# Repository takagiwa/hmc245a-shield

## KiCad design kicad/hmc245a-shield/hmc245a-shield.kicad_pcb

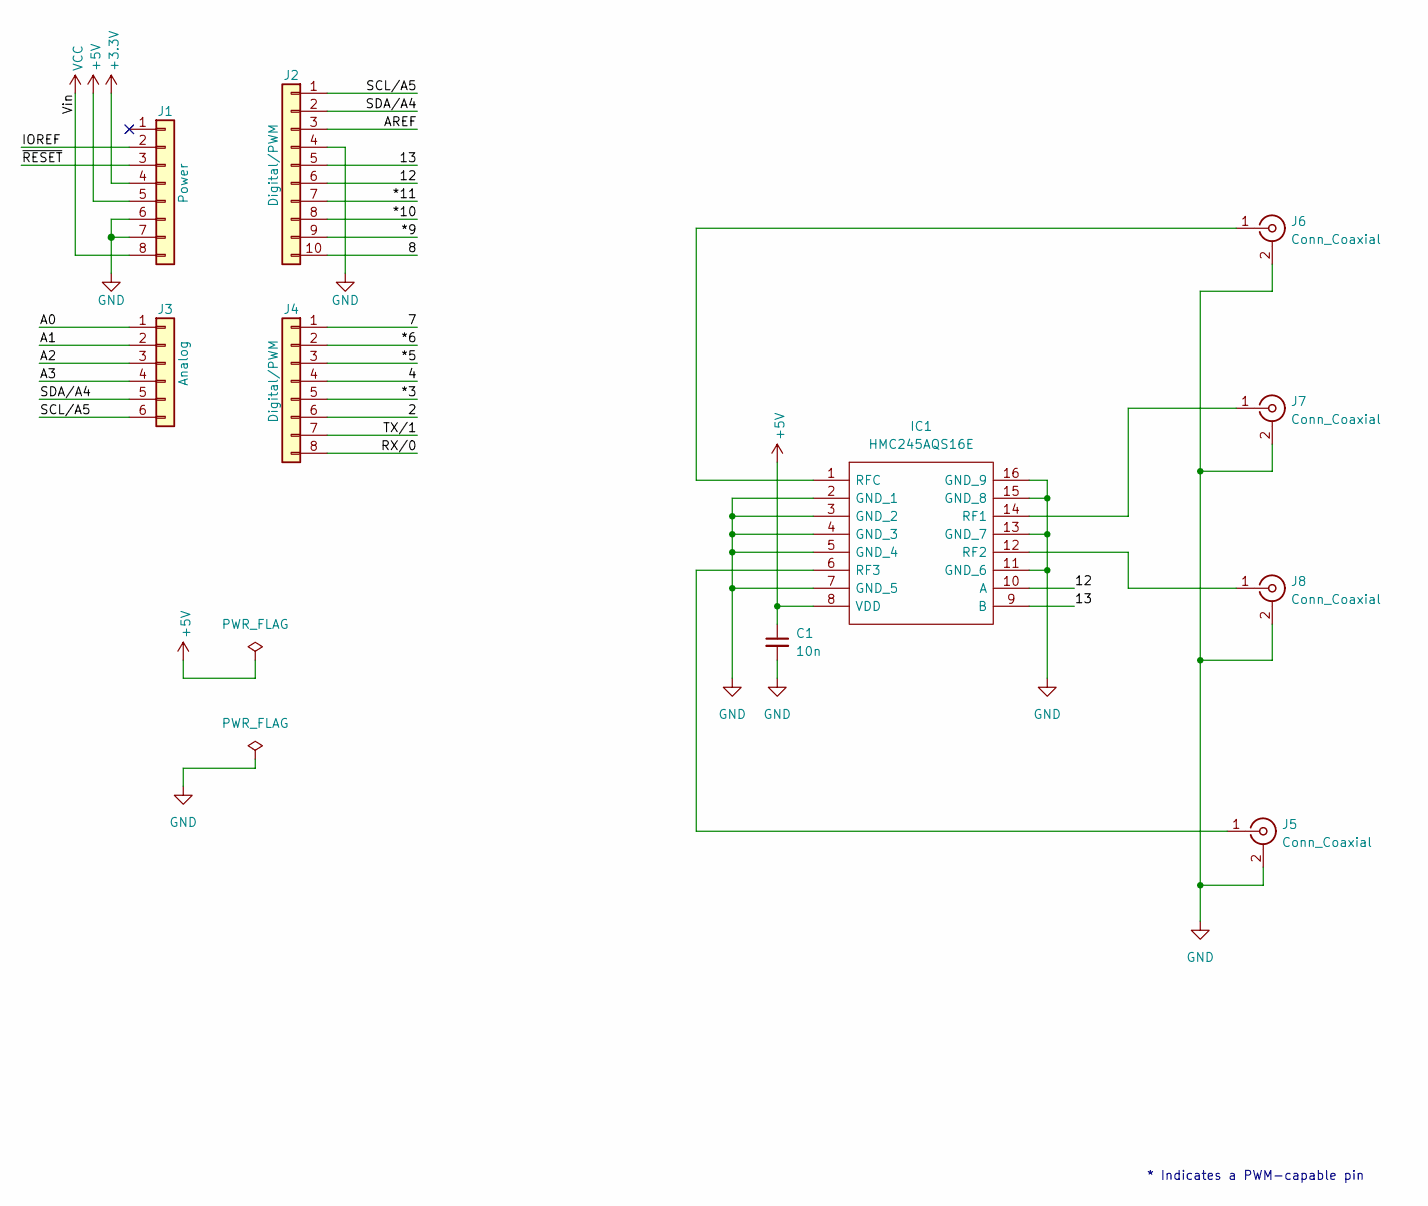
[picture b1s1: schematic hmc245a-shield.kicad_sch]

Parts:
C1: 10n; C_0805_2012Metric_Pad1.18x1.45mm_HandSolder
IC1: HMC245AQS16E; SOP64P600X175-16N; Mouser Part Number 584-HMC245AQS16E
J1: Power; PinSocket_1x08_P2.54mm_Vertical
J2: Digital/PWM; PinSocket_1x10_P2.54mm_Vertical
J3: Analog; PinSocket_1x06_P2.54mm_Vertical
J4: Digital/PWM; PinSocket_1x08_P2.54mm_Vertical
J5, J6, J7, J8: Conn_Coaxial; SMA_Amphenol_901-144_Vertical

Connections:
+3V3: J1.4
+5V: C1.1, IC1.8 (VDD), J1.5
/2: J4.6
/4: J4.4
/7: J4.1
/8: J2.10
/12: IC1.10 (A), J2.6
/13: IC1.9 (B), J2.5
/*3: J4.5
/*5: J4.3
/*6: J4.2
/*9: J2.9
/*10: J2.8
/*11: J2.7
/A0: J3.1
/A1: J3.2
/A2: J3.3
/A3: J3.4
/AREF: J2.3
/IOREF: J1.2
/RX/0: J4.8
/SCL/A5: J2.1, J3.6
/SDA/A4: J2.2, J3.5
/TX/1: J4.7
/~RESET: J1.3
GND: C1.2, IC1.2 (GND_1), IC1.3 (GND_2), IC1.4 (GND_3), IC1.5 (GND_4), IC1.7 (GND_5), IC1.11 (GND_6), IC1.13 (GND_7), IC1.15 (GND_8), IC1.16 (GND_9), J1.6, J1.7, J2.4, J5.2 (Ext), J6.2 (Ext), J7.2 (Ext), J8.2 (Ext)
unnamed: IC1.1 (RFC), J6.1 (In)
unnamed: IC1.6 (RF3), J5.1 (In)
unnamed: IC1.12 (RF2), J8.1 (In)
unnamed: IC1.14 (RF1), J7.1 (In)
VCC: J1.8

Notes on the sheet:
* Indicates a PWM-capable pin

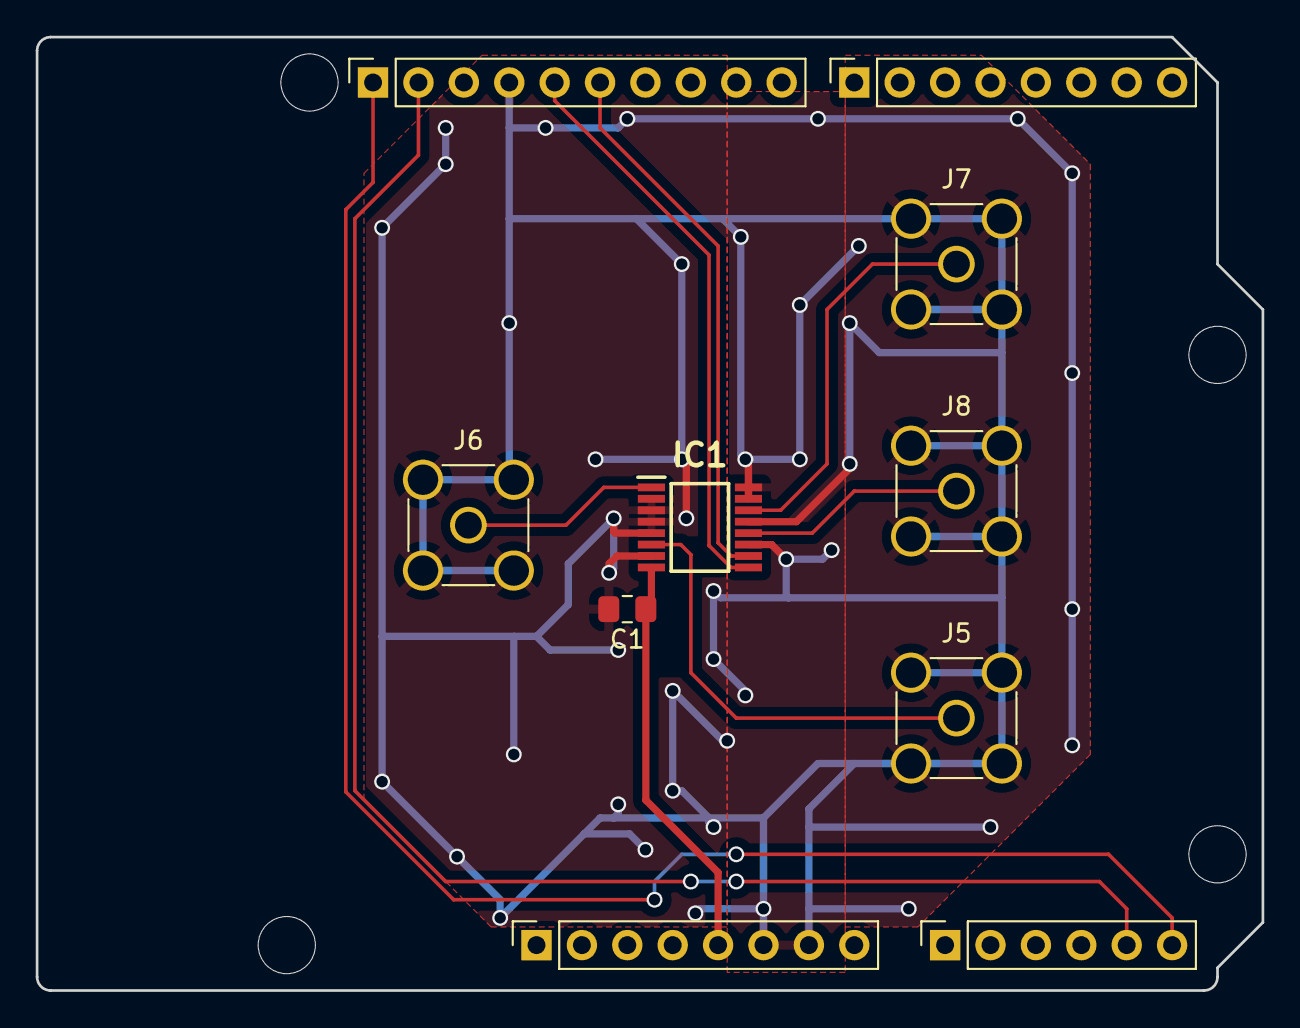
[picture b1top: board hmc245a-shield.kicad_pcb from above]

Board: 2 copper layers, 68.6 x 53.3 mm, 14 parts (0 on the bottom side), 10 nets.

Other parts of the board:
MH1, MH2, MH3, MH4: MountingHole_3.2mm

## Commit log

2023-07-03 ひとまず回路図を描いて部品を置いた
2023-07-03 パターンをひいた
